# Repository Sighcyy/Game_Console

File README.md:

# Game_Console

This project is a custom-built, minimalist handheld game console inspired by the iconic Game Boy Color. Designed from the ground up, it features a compact PCB, a high-quality 3.5” LED display, and a rechargeable lithium-ion battery system—all housed in a sleek, ergonomically designed enclosure.

# Project Overview
Total Time Spent: ~18 hours

After completing two previous electronics projects focused primarily on PCB design and signal routing, I wanted to expand my skills by creating a fully portable device with a display and physical controls. The goal was to build a retro-style gaming device capable of running classic games like Pokémon, Tetris, and Super Mario while embracing a clean and minimalist aesthetic.

Key design decisions included using the Raspberry Pi Zero 2 WH as the main processing unit due to its compact size and emulation capabilities, and choosing an LED screen without integrated audio to simplify the design. The power system was upgraded to a rechargeable lithium-ion battery paired with a boost converter, allowing efficient voltage regulation and easy wiring underneath the Pi board.

Technical Highlights
Compact PCB Layout: Designed under 100x100 mm for cost-effective manufacturing and compactness.

Component Integration: Custom 3D CAD modeling to accommodate the battery, boost converter, microcontroller, and display, ensuring precise fit within a custom enclosure.

Minimalist Design: Removed unnecessary components such as the rotary encoder to maintain a streamlined, user-friendly form factor.

Firmware & Emulation: Leveraged RetroPie, a community-supported emulator platform that supports extensive button configuration, simplifying software setup.

Custom Soldering Documentation: Created unique schematic visualizations to document the process of soldering wires to the underside of the Raspberry Pi Zero 2 WH for a clean internal layout.

# Project Goal
The goal of this project is to create a fully functional, portable retro gaming console that captures the nostalgic feel of classic handheld devices like the Game Boy Color. This involves designing a compact, cost-effective PCB layout under 100x100 mm that integrates the Raspberry Pi Zero 2 WH, a 3.5” LED display, power components, and physical controls. A minimalist yet ergonomic enclosure is developed through precise 3D CAD modeling to securely house all parts while maintaining a sleek form factor. The project also aims to implement a reliable rechargeable power system using a lithium-ion battery and boost converter for consistent voltage delivery. By leveraging open-source emulation software like RetroPie, the console supports a wide range of classic games with easily configurable controls, simplifying the firmware side of the build. Finally, clear documentation of the hardware assembly, including custom wiring and soldering techniques, ensures the design is reproducible and ready for future enhancements.

# BOM

# CAD

# PCB and Shcematic and Wiring

# Firmware

https://retropie.org.uk/

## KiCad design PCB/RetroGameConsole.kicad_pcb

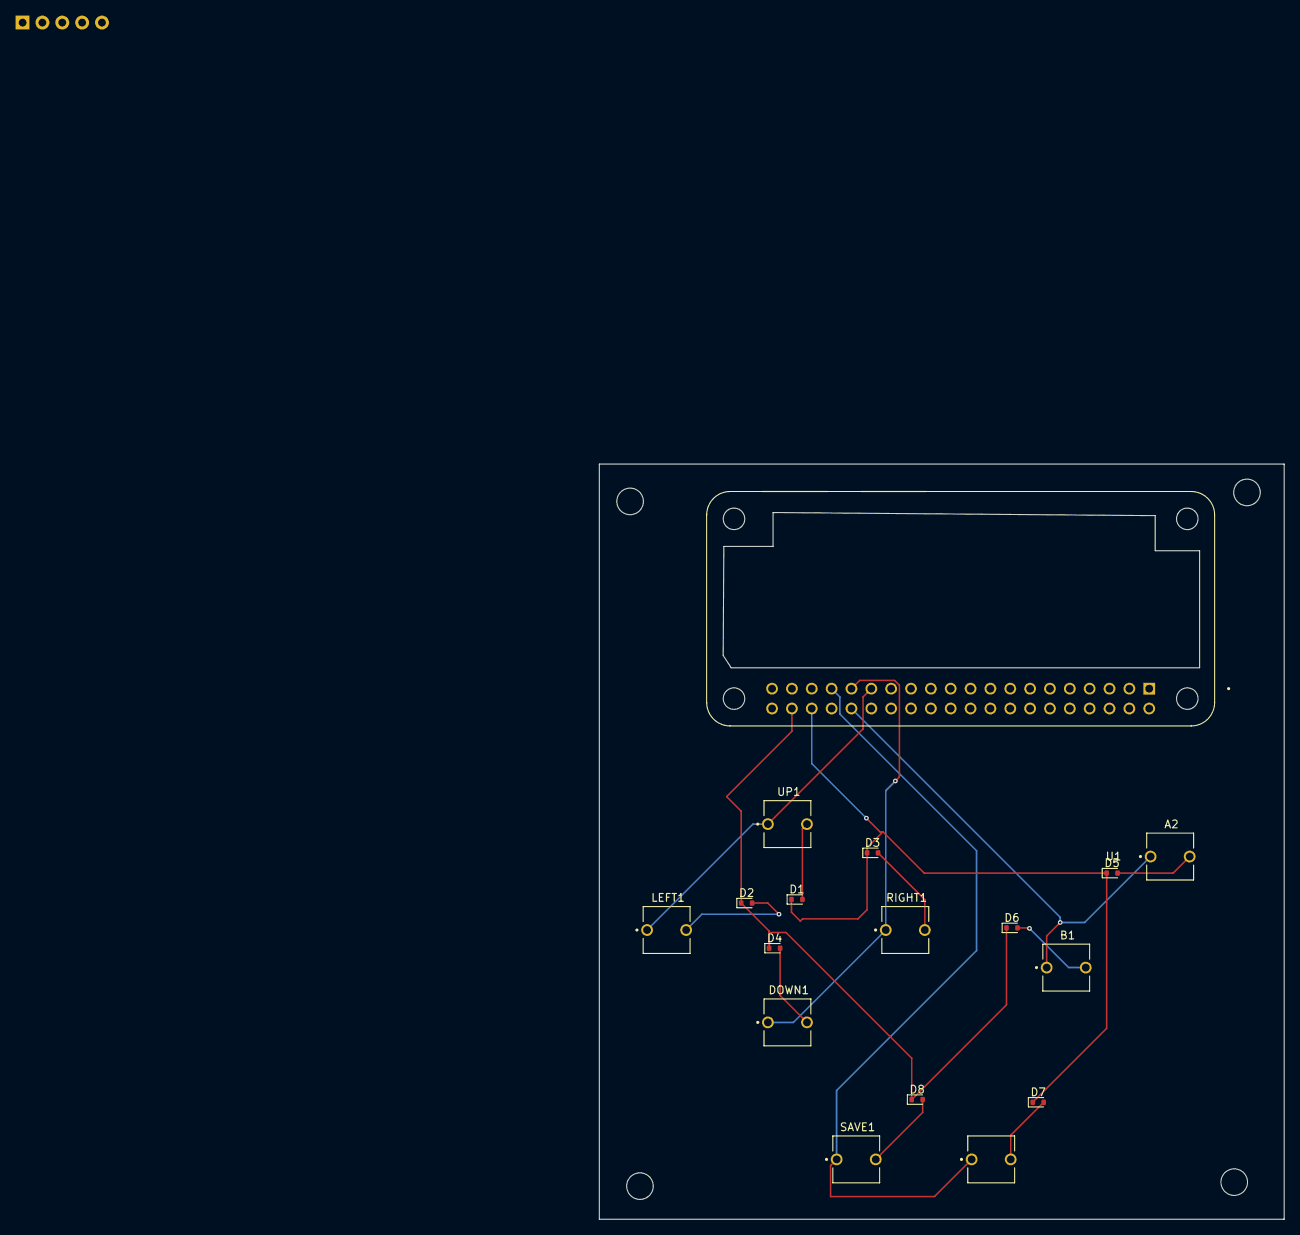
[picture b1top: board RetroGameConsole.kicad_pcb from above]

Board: 2 copper layers, 87.6 x 96.6 mm, 18 parts (0 on the bottom side), 14 nets.

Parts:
A2: BUTT-2; SW_BUTT-2
B1: BUTT-2; SW_BUTT-2
D1, D2, D3, D4, D5, D6, D7, D8: 1N4148WT; D_SOD-523
DOWN1: BUTT-2; SW_BUTT-2
LEFT1: BUTT-2; SW_BUTT-2
RIGHT1: BUTT-2; SW_BUTT-2
SAVE1: BUTT-2; SW_BUTT-2
SELECT1: BUTT-2; SW_BUTT-2
U1: RASPBERRY_PI_ZERO_2_W; MODULE_RASPBERRY_PI_ZERO_2_W
U2: PAM8302AASCR; 1X05_ROUND_70
UP1: BUTT-2; SW_BUTT-2

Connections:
Column1: LEFT1.1, U1.29 (GPIO5), UP1.1
Column2: DOWN1.1, RIGHT1.1, U1.31 (GPIO6)
Column3: A2.1, B1.1, U1.32 (GPIO12)
Column4: SAVE1.1, SELECT1.1, U1.33 (GPIO13)
unnamed: D1.2 (A), UP1.2
unnamed: D2.2 (A), LEFT1.2
unnamed: D3.2 (A), RIGHT1.2
unnamed: D4.2 (A), DOWN1.2
unnamed: A2.2, D5.2 (A)
unnamed: B1.2, D6.2 (A)
unnamed: D7.2 (A), SELECT1.2
unnamed: D8.2 (A), SAVE1.2
Row1: D1.1 (K), D3.1 (K), D5.1 (K), D7.1 (K), U1.36 (GPIO16)
Row2: D2.1 (K), D4.1 (K), D6.1 (K), D8.1 (K), U1.38 (GPIO20)

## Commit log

2025-07-20 Create yes
2025-07-20 Create ys
2025-07-20 Create yesyes
2025-07-20 Update and rename yes to RetroPie OS Information
2025-07-20 Rename ys to ys.md
2025-07-20 Rename ys.md to RetroPie.md
